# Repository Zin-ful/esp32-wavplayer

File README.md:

This repo consists of a KiCad schematic + model and the code needed to create an ESP32-C3 Mp3 style audio player with a focus on the wav format.

GPIO1  -> PCM5102A BCK  T#2
-
GPIO2  -> PCM5102A LRCK T#3
-
GPIO3  -> PCM5102A DATA T#4
-

GPIO4  -> SD SCK        T#5
-
GPIO5  -> SD MISO       B#1
-
GPIO6  -> SD MOSI       B#2
-
GPIO7  -> SD CS         B#3
-

GPIO8  -> OLED SDA      B#4
-
GPIO9  -> OLED SCL      B#5
-

PCM5102A BCK  GPIO1 ACD1_1
-
PCM5102A LRCK GPIO2 ACD1_2
-
PCM5102A DATA GPIO3 ACD1_3
-
PCM5102A 3.3V 3.3V
-
PCM5102A GND  GND
-
SD       SCK  GPIO4 A4 / SCK
-
SD       MISO GPIO5 A5 / MISO
-
SD       MOSI GPIO6 MOSI
-
SD       CS   GPIO7 SS/CS
-
SSD1306  SDA  GPIO8 SDA
-
SSD1306  SCL  GPIO9 SCL
-

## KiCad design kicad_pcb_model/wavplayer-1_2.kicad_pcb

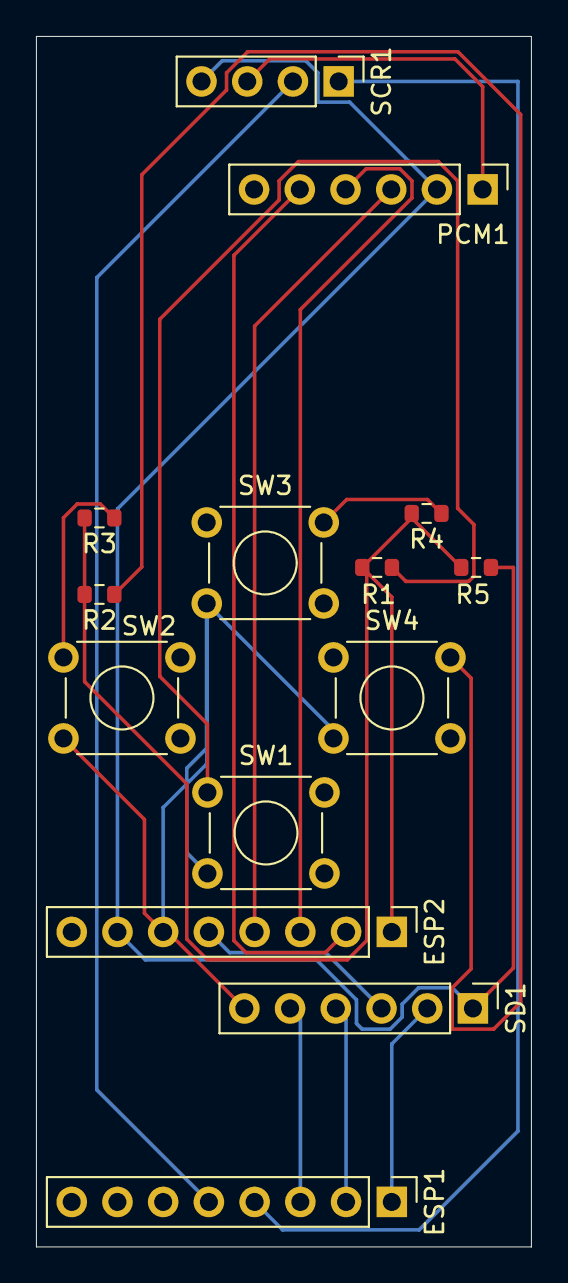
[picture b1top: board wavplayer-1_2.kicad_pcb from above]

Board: 2 copper layers, 27.5 x 67.2 mm, 14 parts (0 on the bottom side), 16 nets.

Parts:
ESP1: ESP32_C3_SuperMini_Right; PinHeader_1x08_P2.54mm_Vertical
ESP2: ESP32_C3_SuperMini_Left; PinHeader_1x08_P2.54mm_Vertical
PCM1: PCM5102a_Genaric; PinHeader_1x06_P2.54mm_Vertical
R1: 1.5k; R_0603_1608Metric
R2: 5.1k; R_0603_1608Metric
R3: 6.8k; R_0603_1608Metric
R4, R5: 10k; R_0603_1608Metric
SCR1: SSD1306; PinHeader_1x04_P2.54mm_Vertical
SD1: SDcard_Generic; PinHeader_1x06_P2.54mm_Vertical
SW1: DOWN; SW_TH_Tactile_Omron_B3F-100x
SW2: BACK; SW_TH_Tactile_Omron_B3F-100x
SW3: UP; SW_TH_Tactile_Omron_B3F-100x
SW4: ENTER; SW_TH_Tactile_Omron_B3F-100x

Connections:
+3V3: ESP2.6, PCM1.1, SCR1.3, SD1.6, SW1.2, SW2.2, SW3.2, SW4.2
/CS: ESP1.3, SD1.5
/GP0_ADC1_0: ESP2.1, R1.2, R2.2, R3.2, R4.2, R5.2
/GP1_ADC1_1: ESP2.2, PCM1.5
/GP2_ADC1_2: ESP2.3, PCM1.4
/GP3_ADC1_3: ESP2.4, PCM1.3
/MISO: ESP1.1, SD1.2
/MOSI: ESP1.2, SD1.4
/SCK: ESP2.5, SD1.3
/SCL: ESP1.5, SCR1.2
/SDA: ESP1.4, SCR1.1
GND: ESP2.7, PCM1.2, R5.1, SCR1.4, SD1.1
unnamed: R1.1, SW1.1
unnamed: R2.1, SW4.1
unnamed: R3.1, SW2.1
unnamed: R4.1, SW3.1

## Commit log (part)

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2026-05-26 card formatting, scrolling, filesystem
2026-05-27 added back button
2026-05-28 lowering memory foot print, back button, sleep modes
2026-05-28 putting in audio func
2026-06-01 added audio playback - untested
2026-06-09 plays sounds, reoganized, refined
    added new item for current song info
    changed pin assignment
    added a new no-block delay to allow playing while waiting
    re arranged function location
    a bunch of other shit
2026-06-10 UI and Input improvements
    auto update screen on song end
    removed draw_progress delay in favor for checking for a pixel change
    this also fixes inconsistent inputs
    moved LS to only when a card is mounted to avoid repeated loops every time a user enters a menu
2026-06-10 adding pause button
    added a visual for pausing and making it persistent if you leave and return to the player menu
2026-06-12 slowed sd card SPI, analog input
    swapped from digital input to analog to allow resistor ladder based input systems
2026-06-13 Rename esp32-wavplayer.ino to src/esp32-wavplayer.ino
2026-06-13 Rename fp-lib-table to kicad_pcb_model/fp-lib-table
2026-06-13 Rename wavplayer-1_0.kicad_pcb to kicad_pcb_model/wavplayer-1_0.kicad_pcb
2026-06-13 Rename wavplayer-1_0.kicad_prl to kicad_pcb_model/wavplayer-1_0.kicad_prl
2026-06-13 Rename wavplayer-1_0.kicad_pro to kicad_pcb_model/wavplayer-1_0.kicad_pro
2026-06-13 Rename wavplayer-1_0.kicad_sch to kicad_pcb_model/wavplayer-1_0.kicad_sch
2026-06-13 Rename src/esp32-wavplayer.ino to src/esp32-wroom-32d/esp32-wavplayer.ino
